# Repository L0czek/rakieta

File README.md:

Rakieta hardware
================

This repository contains the hardware and firmware for the rocket engine test project. It groups several PCBs and related firmware used for sensing, control distribution, ignition, and a crash-survivable blackbox recorder.

Subprojects

- `blackbox/`: Blackbox PCB (stores UART data to SD card)
- `blackbox-firmware/`: Firmware for the blackbox recorder
- `connector-main-computer/`: Connector board near controller that aggregates GPIO to a 10m DVI-I cable
- `connector-test-stand/`: Connector board at the test-stand end; decomposes signals, provides power, analog preprocessing, and actuators
- `esp32-mainboard/`: ESP32-C6 controller firmware as a git submodule on the `teststand` branch
- `frontend/`: Web UI for telemetry visualization and command/control; connects to MQTT over WebSocket
- `sensor-tmp107/`: TMP107 temperature sensor PCB (chainable via SMAART wire bus)
- `starter/`: Ignition starter board with I2C IO expander and safety comparator

Connection graph (Mermaid)

```mermaid
flowchart TB;
CONTROLLER["`CONTROLLER
esp32-mainboard`"] --- id(MAIN COMPUTER CONNECTOR)
CONTROLLER --- BLACKBOX
CONTROLLER ---|WiFi| MQTT[("`MQTT SERVER
eclipse-mosquitto`")]
id(MAIN COMPUTER CONNECTOR) --- id10(SAFETY BUTTON)
id(MAIN COMPUTER CONNECTOR) ---|10m DVI-I cable| id2(TEST STAND CONNECTOR)
id6(12V AGM battery) --- id2(TEST STAND CONNECTOR)
id2(TEST STAND CONNECTOR) --- id3(TEMP SENSOR 1)
id3(TEMP SENSOR 1) --- id4[[TEMP SENSOR 2...]]
id2(TEST STAND CONNECTOR) --- id5(STARTER)
id2(TEST STAND CONNECTOR) --- id7[[PRESSURE SENSORS 1 & 2]]
id2(TEST STAND CONNECTOR) --- id8(VALVE SERVO)
id2(TEST STAND CONNECTOR) --- id11(TENSOMETR)
id5(STARTER) --- id9(ENGINE IGNITION)
FRONTEND[[FRONTEND WEB UI]] --- MQTT
```

MQTT communication

- Broker: Mosquitto (`docker-compose.yml` service `mqtt`)
- Frontend: Docker Compose also launches the web dashboard on `http://localhost:3000`
- Controller (`esp32-mainboard`) publishes telemetry and receives command topics via MQTT
- Controller also publishes raw `defmt` log bytes on `log/defmt`
- The matching firmware ELF is shared as retained raw bytes on
  `shared/firmware/test_stand_controller/elf`
- Frontend connects to the same broker via WebSocket (`ws://<host>:8000`) and subscribes/publishes control topics
- MQTT TCP port: `1883` (standard MQTT)
- MQTT WebSocket port: `8000` (used by frontend)
- `mosquitto.conf` raises `max_packet_size` to `20000000` so the retained
  `shared/firmware/test_stand_controller/elf` payload can carry the matching firmware ELF

Publishing the retained ELF

Use the helper script after building the matching controller firmware ELF:

```bash
scripts/publish-test-stand-elf.sh \
  esp32-mainboard/target/riscv32imac-unknown-none-elf/debug/test_stand_controller
```

Set `MQTT_HOST`, `MQTT_PORT`, `MQTT_USERNAME`, `MQTT_PASSWORD`, or `MQTT_TOPIC` if you need
non-default broker settings.

Running with Docker Compose

```bash
git submodule update --init --recursive
docker compose up --build
```

The frontend is available at `http://localhost:3000`. The MQTT broker exposes TCP MQTT on
`1883` and WebSocket MQTT on `8000`.

Notes

- This repo is intended for hardware files (KiCad projects), gerbers and firmware sources related to the test-stand and engine instrumentation.
- See subdirectory READMEs for purpose and quick pointers to major files.

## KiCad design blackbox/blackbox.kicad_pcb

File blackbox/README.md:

Blackbox PCB
============

Purpose

The `blackbox` board is a crash-survivable data logger. It receives UART data from the controller and writes received data to an SD card so launch telemetry can be retrieved after a failure.

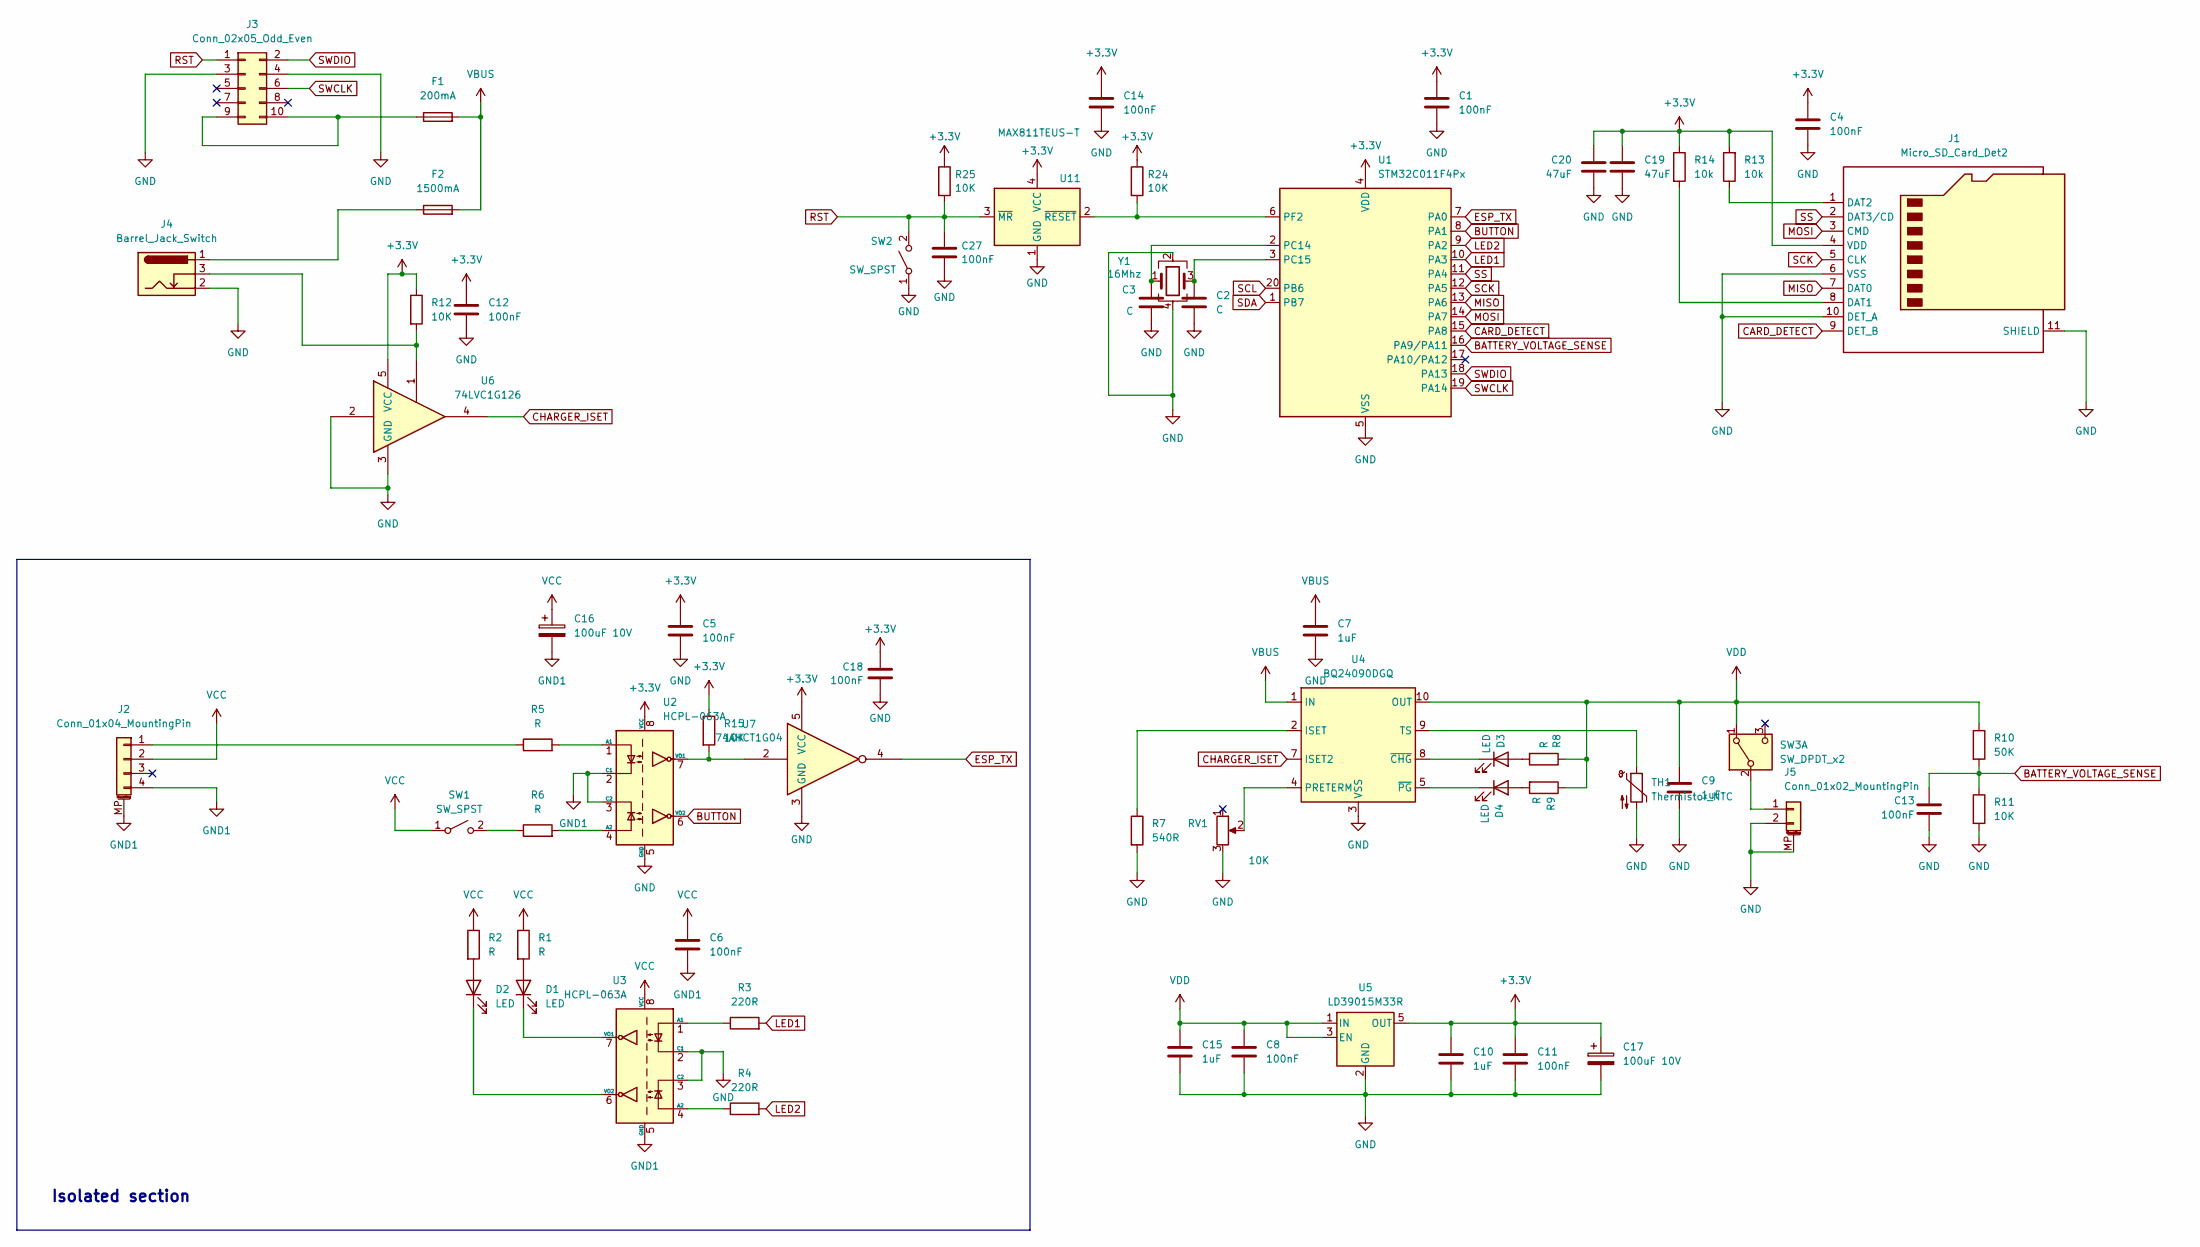
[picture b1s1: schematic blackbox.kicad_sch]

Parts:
C1, C4, C5, C6, C8, C11, C12, C13, C14, C18, C27: 100nF; C_0805_2012Metric
C2, C3: C; C_0805_2012Metric
C7, C9, C10, C15: 1uF; C_1206_3216Metric
C16, C17: 100uF 10V; CP_Elec_5x5.4
C19, C20: 47uF; C_1206_3216Metric
D1, D2: LED; LED_D5.0mm_Horizontal_O3.81mm_Z9.0mm
D3, D4: LED; LED_0805_2012Metric
F1: 200mA; Fuse_1206_3216Metric
F2: 1500mA; Fuse_1206_3216Metric
J1: Micro_SD_Card_Det2; microSD_HC_Hirose_DM3BT-DSF-PEJS
J2: Conn_01x04_MountingPin; JST_PH_S4B-PH-SM4-TB_1x04-1MP_P2.00mm_Horizontal
J3: Conn_02x05_Odd_Even; IDC-Header_2x05_P2.54mm_Vertical
J4: Barrel_Jack_Switch; BarrelJack_Horizontal
J5: Conn_01x02_MountingPin; JST_PH_S2B-PH-SM4-TB_1x02-1MP_P2.00mm_Horizontal
R1, R2, R5, R6, R8, R9: R; R_0805_2012Metric
R3, R4: 220R; R_0805_2012Metric
R7: 540R; R_0805_2012Metric
R10: 50K; R_0805_2012Metric
R11, R12, R15, R24, R25: 10K; R_0805_2012Metric
R13, R14: 10k; R_0805_2012Metric
RV1: 10K; Potentiometer_Bourns_3314J_Vertical
SW1: SW_SPST; SW_Tactile_SPST_Angled_PTS645Vx31-2LFS
SW2: SW_SPST; SW_SPST_B3S-1000
SW3: SW_DPDT_x2; SW_DPDT_CK_JS202011JCQN
TH1: Thermistor_NTC; R_0603_1608Metric
U1: STM32C011F4Px; TSSOP-20_4.4x6.5mm_P0.65mm
U2, U3: HCPL-063A; SOIC-8_3.9x4.9mm_P1.27mm
U4: BQ24090DGQ; IC_XTR111AIDGQR
U5: LD39015M33R; SOT-23-5
U6: 74LVC1G126; SOT-23-5
U7: 74AHCT1G04; SOT-23-5
U11: MAX811TEUS-T; SOT-143
Y1: 16Mhz; Crystal_SMD_3225-4Pin_3.2x2.5mm

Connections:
+3.3V: C1.1, C4.1, C5.1, C10.1, C11.1, C12.1, C14.1, C17.1, C18.1, C19.1, C20.1, J1.4 (VDD), R12.1, R13.2, R14.1, R15.1, R24.1, R25.1, U1.4 (VDD), U2.8 (VCC), U5.5 (OUT), U6.5 (VCC), U7.5 (VCC), U11.4 (VCC)
BATTERY_VOLTAGE_SENSE: C13.2, R10.2, R11.1, U1.16 (PA9/PA11)
BUTTON: U1.8 (PA1), U2.6 (VO2)
CARD_DETECT: J1.9 (DET_B), U1.15 (PA8)
CHARGER_ISET: U4.7 (ISET2), U6.4
ESP_TX: U1.7 (PA0), U7.4
GND: C1.2, C2.2, C3.2, C4.2, C5.2, C7.2, C8.2, C9.2, C10.2, C11.2, C12.2, C13.1, C14.2, C15.2, C17.2, C18.2, C19.2, C20.2, C27.2, J1.6 (VSS), J1.10 (DET_A), J1.11 (SHIELD), J3.3, J3.4, J4.2, J5.2, J5.MP (MountPin), R7.2, R11.2, RV1.3, SW2.1 (A), TH1.2, U1.5 (VSS), U2.5 (GND), U3.2 (C1), U3.3 (C2), U4.3 (VSS), U4.11 (VSS), U5.2 (GND), U6.2, U6.3 (GND), U7.3 (GND), U11.1 (GND), Y1.2, Y1.4
GND1: C6.2, C16.2, J2.4, J2.MP (MountPin), U2.2 (C1), U2.3 (C2), U3.5 (GND)
LED1: R3.2, U1.10 (PA3)
LED2: R4.2, U1.9 (PA2)
MISO: J1.7 (DAT0), U1.13 (PA6)
MOSI: J1.3 (CMD), U1.14 (PA7)
unnamed: D1.2 (A), R1.2
unnamed: D1.1 (K), U3.7 (VO1)
unnamed: D2.2 (A), R2.2
unnamed: D2.1 (K), U3.6 (VO2)
unnamed: D3.2 (A), R8.2
unnamed: D3.1 (K), U4.8 (~CHG)
unnamed: D4.2 (A), R9.2
unnamed: D4.1 (K), U4.5 (~PG)
unnamed: F2.1, J4.1
unnamed: J1.8 (DAT1), R14.2
unnamed: J1.1 (DAT2), R13.1
unnamed: J2.1, R5.1
unnamed: F1.1, J3.9, J3.10
unnamed: J4.3, R12.2, U6.1
unnamed: J5.1, SW3.2 (B)
unnamed: R6.1, SW1.2 (B)
unnamed: C3.1, U1.2 (PC14), Y1.1
unnamed: C2.1, U1.3 (PC15), Y1.3
unnamed: R24.2, U1.6 (PF2), U11.2 (~RESET)
unnamed: R5.2, U2.1 (A1)
unnamed: R6.2, U2.4 (A2)
unnamed: R15.2, U2.7 (VO1), U7.2
unnamed: R3.1, U3.1 (A1)
unnamed: R4.1, U3.4 (A2)
unnamed: R7.1, U4.2 (ISET)
unnamed: RV1.2, U4.4 (PRETERM)
unnamed: TH1.1, U4.9 (TS)
RST: C27.1, J3.1, R25.2, SW2.2 (B), U11.3 (~MR)
SCK: J1.5 (CLK), U1.12 (PA5)
SCL: U1.20 (PB6)
SDA: U1.1 (PB7)
SS: J1.2 (DAT3/CD), U1.11 (PA4)
SWCLK: J3.6, U1.19 (PA14)
SWDIO: J3.2, U1.18 (PA13)
VBUS: C7.1, F1.2, F2.2, U4.1 (IN)
VCC: C6.1, C16.1, J2.2, R1.1, R2.1, SW1.1 (A), U3.8 (VCC)
VDD: C8.1, C9.1, C15.1, R8.1, R9.1, R10.1, SW3.1 (A), U4.10 (OUT), U5.1 (IN), U5.3 (EN)

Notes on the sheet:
Isolated section

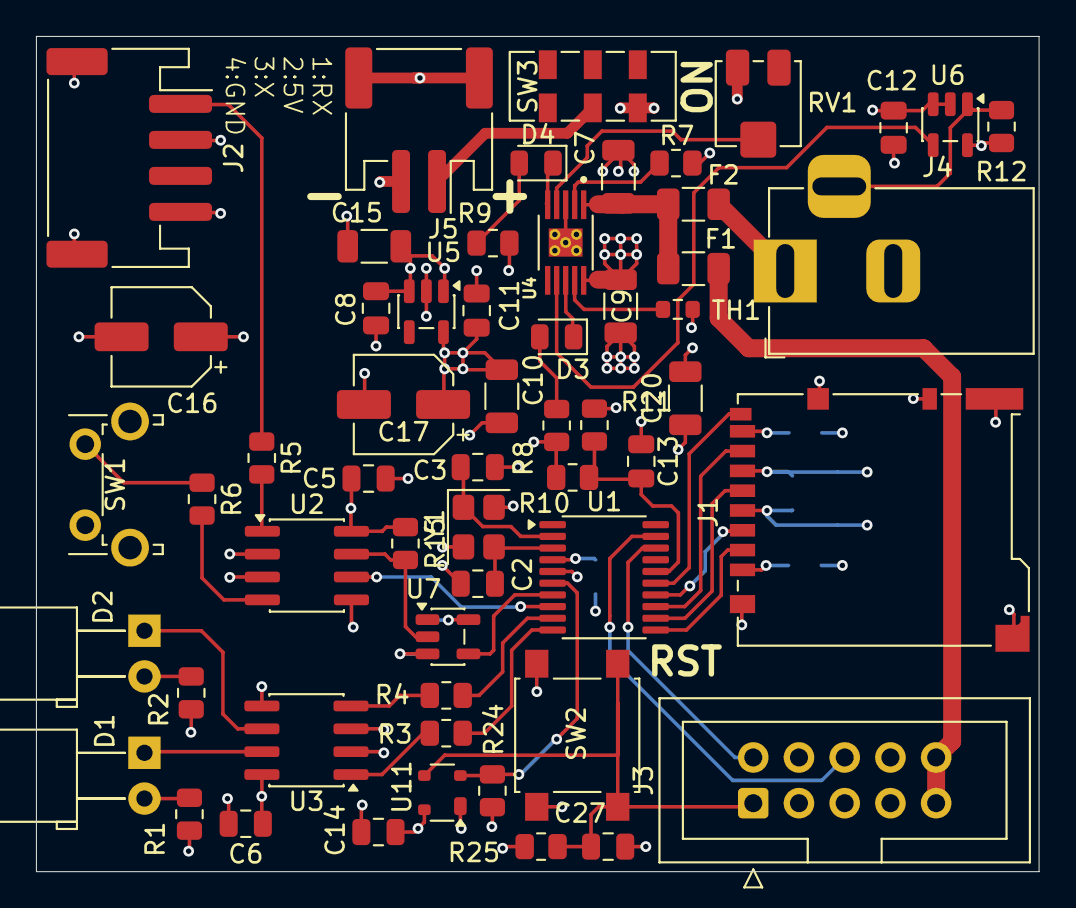
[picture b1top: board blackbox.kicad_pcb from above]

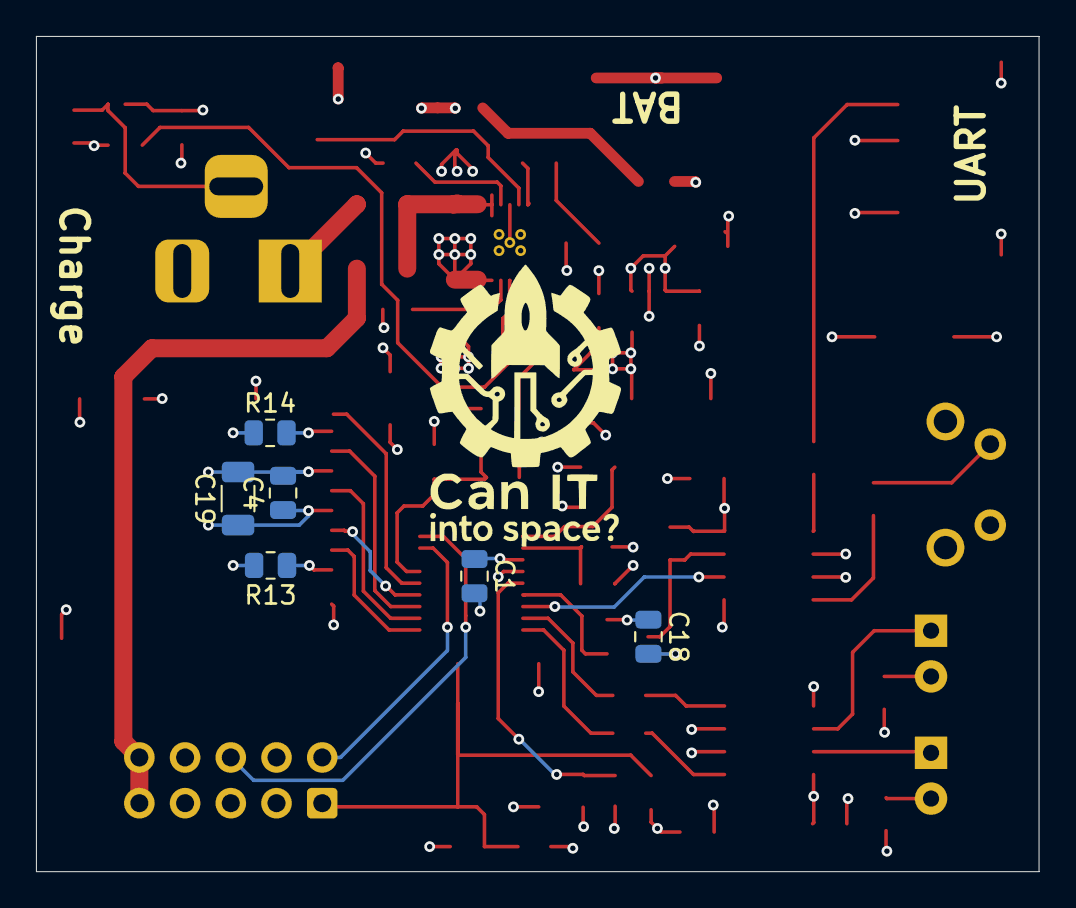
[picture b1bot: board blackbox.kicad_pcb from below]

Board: 4 copper layers, 55.7 x 46.4 mm, 63 parts (6 on the bottom side), 47 nets.

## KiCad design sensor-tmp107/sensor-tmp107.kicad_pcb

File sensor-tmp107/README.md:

TMP107 temperature sensor board
================================

Purpose

This board implements a temperature sensor using the TMP107 device. Multiple boards can be chained in series using the Ti SMAART wire bus (a UART half-duplex bus) to provide temperature sensing along the test-stand.

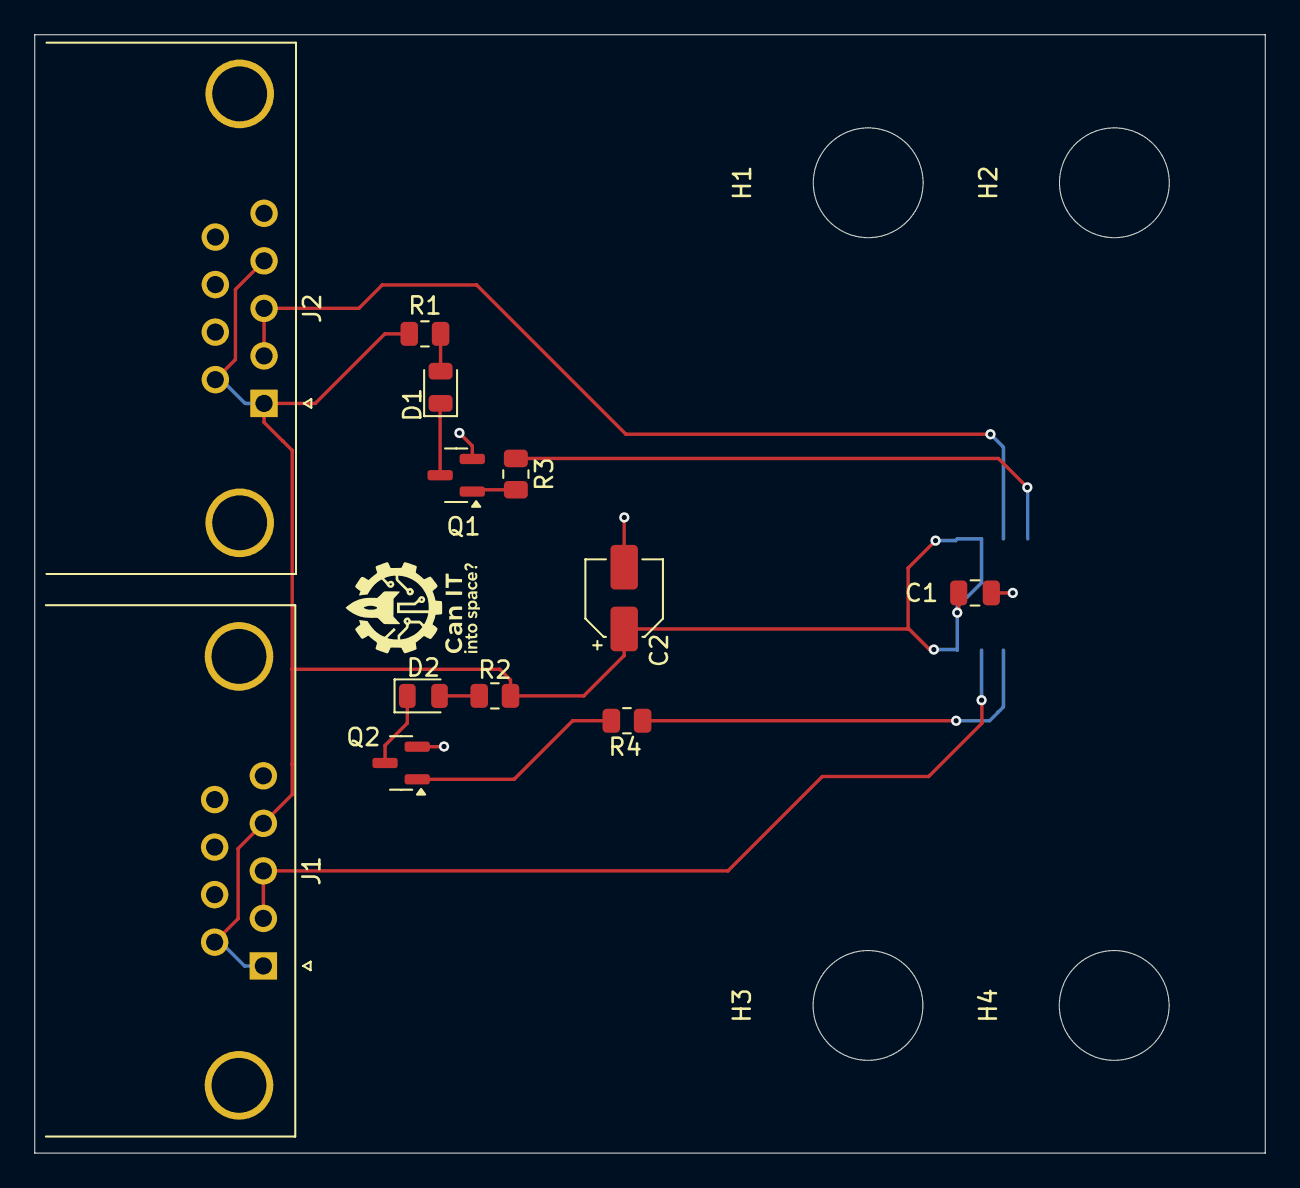
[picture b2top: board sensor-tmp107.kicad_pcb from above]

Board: 2 copper layers, 71.7 x 65.2 mm, 17 parts (1 on the bottom side), 12 nets.

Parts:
C1: 100nF; C_0805_2012Metric
C2: 10uF; CP_Elec_4x5.4
D1: LED żółtozielony; LED_0805_2012Metric
D2: LED czerwony; LED_0805_2012Metric
H1, H2, H3, H4: MountingHole_Pad_MP; MountingHole_6.4mm_M6
J1, J2: DE9_Socket_MountingHoles; DSUB-9_Socket_Horizontal_P2.77x2.84mm_EdgePinOffset9.90mm_H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
Q1, Q2: MMBT3904; SOT-23
R1, R2: 200; R_0805_2012Metric
R3, R4: 10k; R_0805_2012Metric
U1: TMP107BIDR; SOIC127P599X175-8N

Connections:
/5V: C1.1, C2.1, J1.1, J1.4, J1.6, J2.1, J2.4, J2.6, R1.1, R2.1, U1.1 (V+), U1.2 (R1), U1.8 (R2)
GND: C1.2, C2.2, J1.0 (PAD), J1.5, J1.7, J1.8, J1.9, J2.0 (PAD), J2.5, J2.7, J2.8, J2.9, Q1.2 (E), Q2.2 (E), U1.5 (GND)
unnamed: D1.2 (A), R1.2
unnamed: D1.1 (K), Q1.3 (C)
unnamed: D2.2 (A), R2.2
unnamed: D2.1 (K), Q2.3 (C)
unnamed: Q1.1 (B), R3.2
unnamed: Q2.1 (B), R4.1
unnamed: R3.1, U1.4 (ALERT1)
unnamed: R4.2, U1.6 (ALERT2)
unnamed: J2.2, J2.3, U1.3 (I/O1)
unnamed: J1.2, J1.3, U1.7 (I/O2)

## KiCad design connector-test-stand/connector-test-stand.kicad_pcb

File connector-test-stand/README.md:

Connector - test stand
======================

Purpose

This board is the test-stand end of the 10 m DVI-I cable. It decomposes the aggregated parallel bus into individual sensor and effector connectors, performs early analog preprocessing, provides power distribution, and drives actuators such as the valve servo.

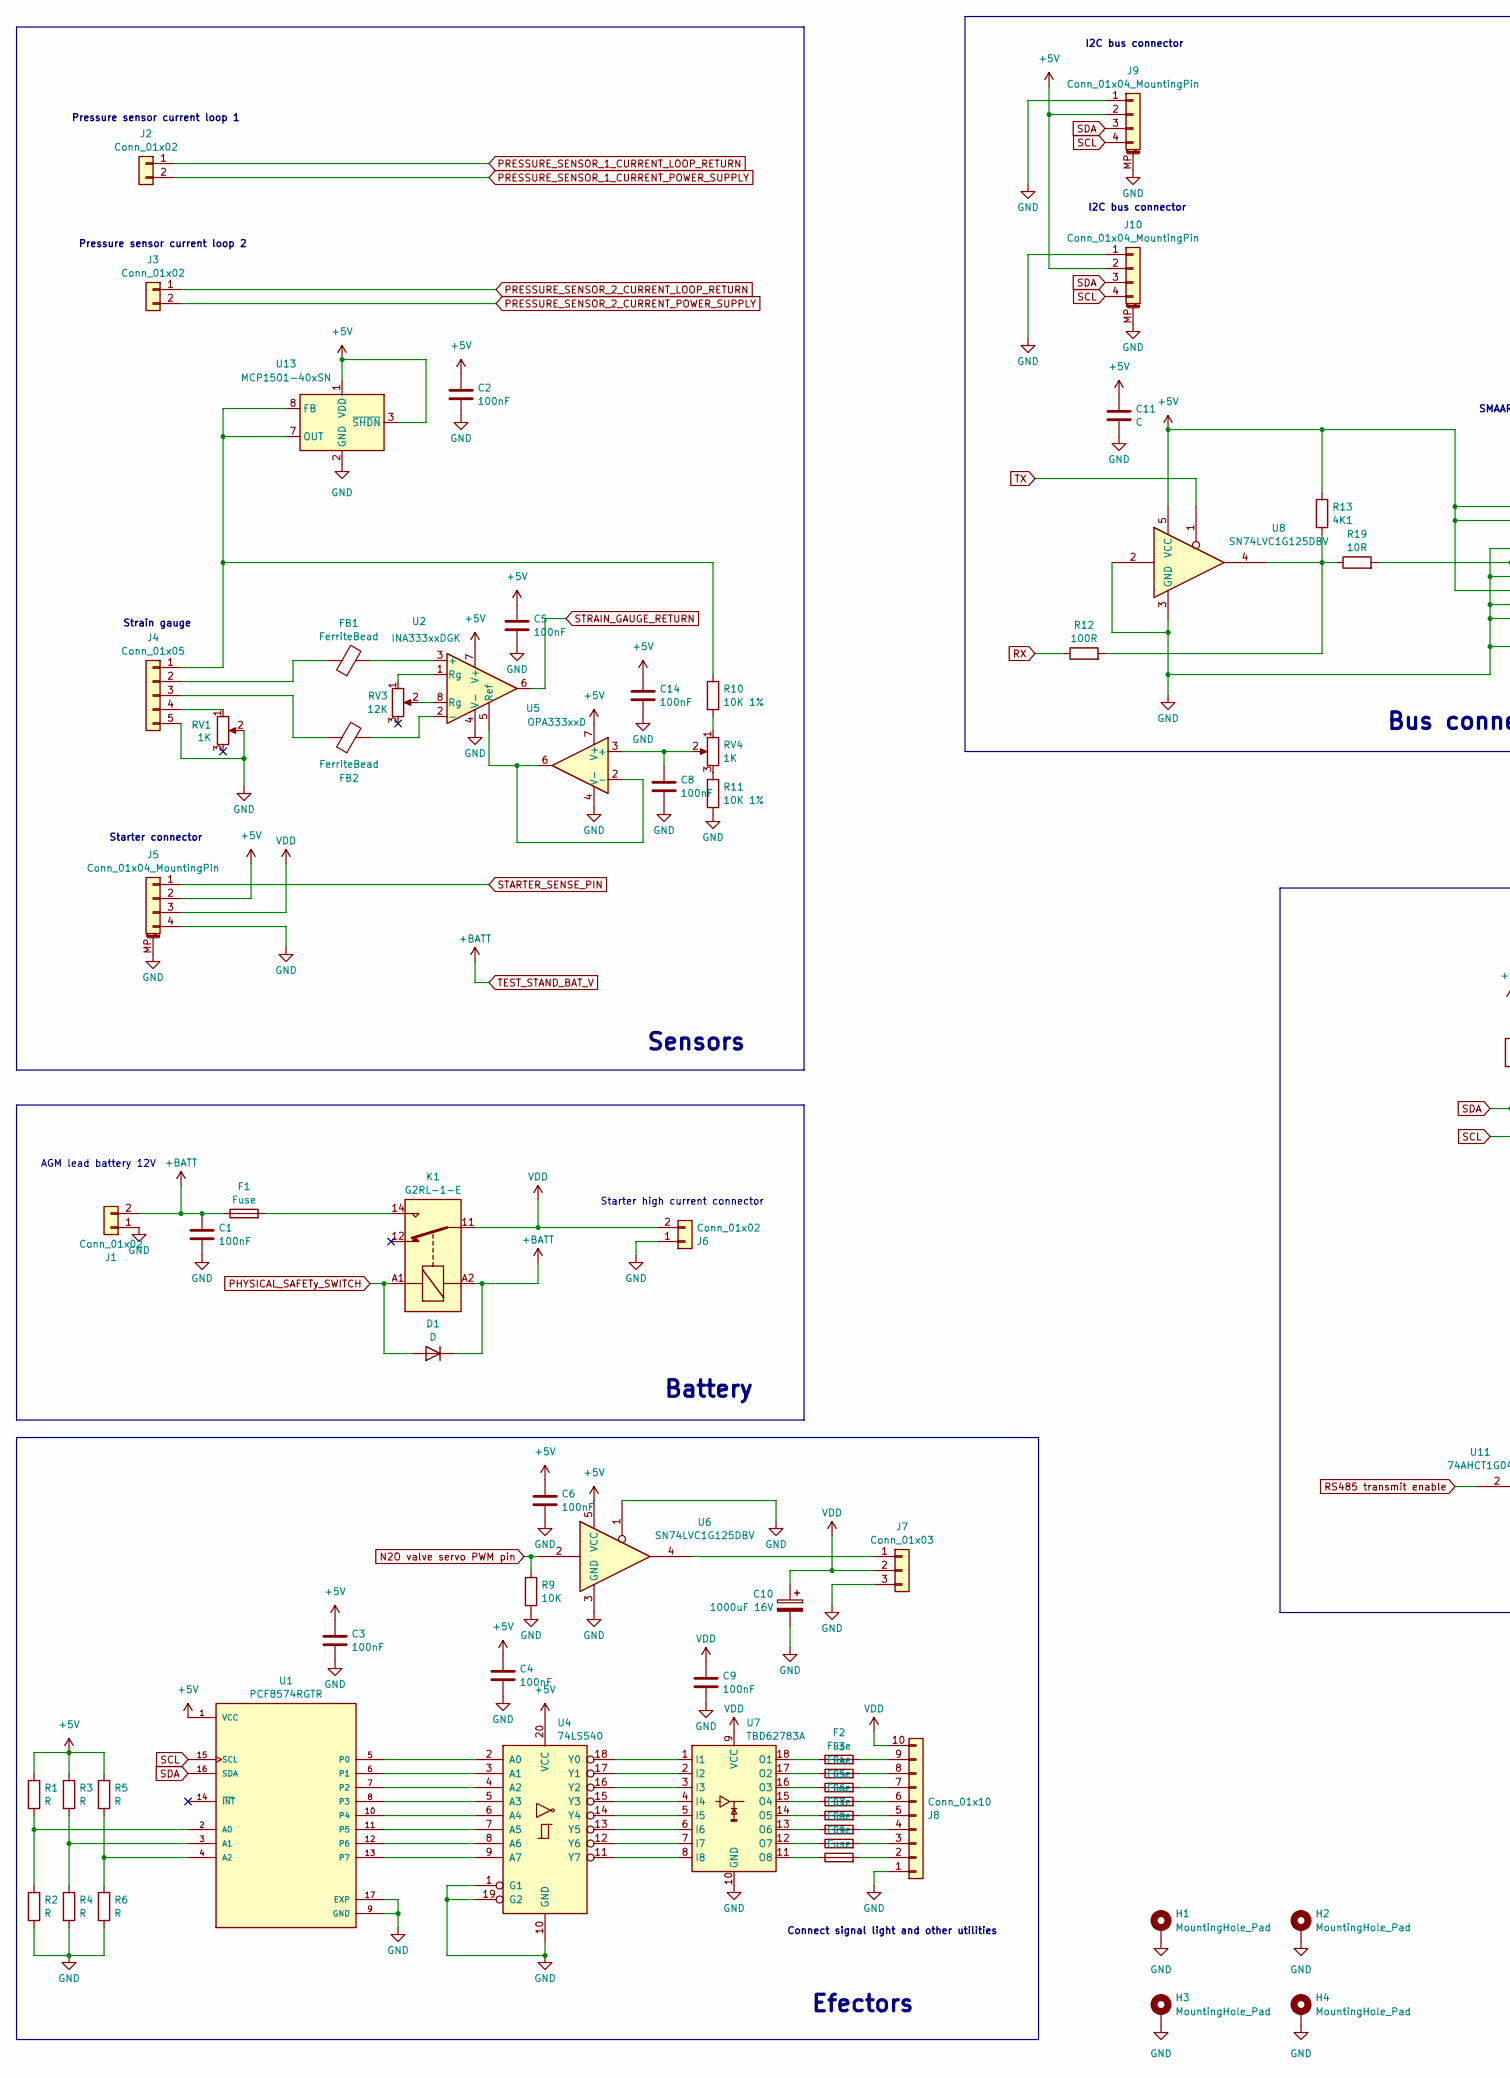
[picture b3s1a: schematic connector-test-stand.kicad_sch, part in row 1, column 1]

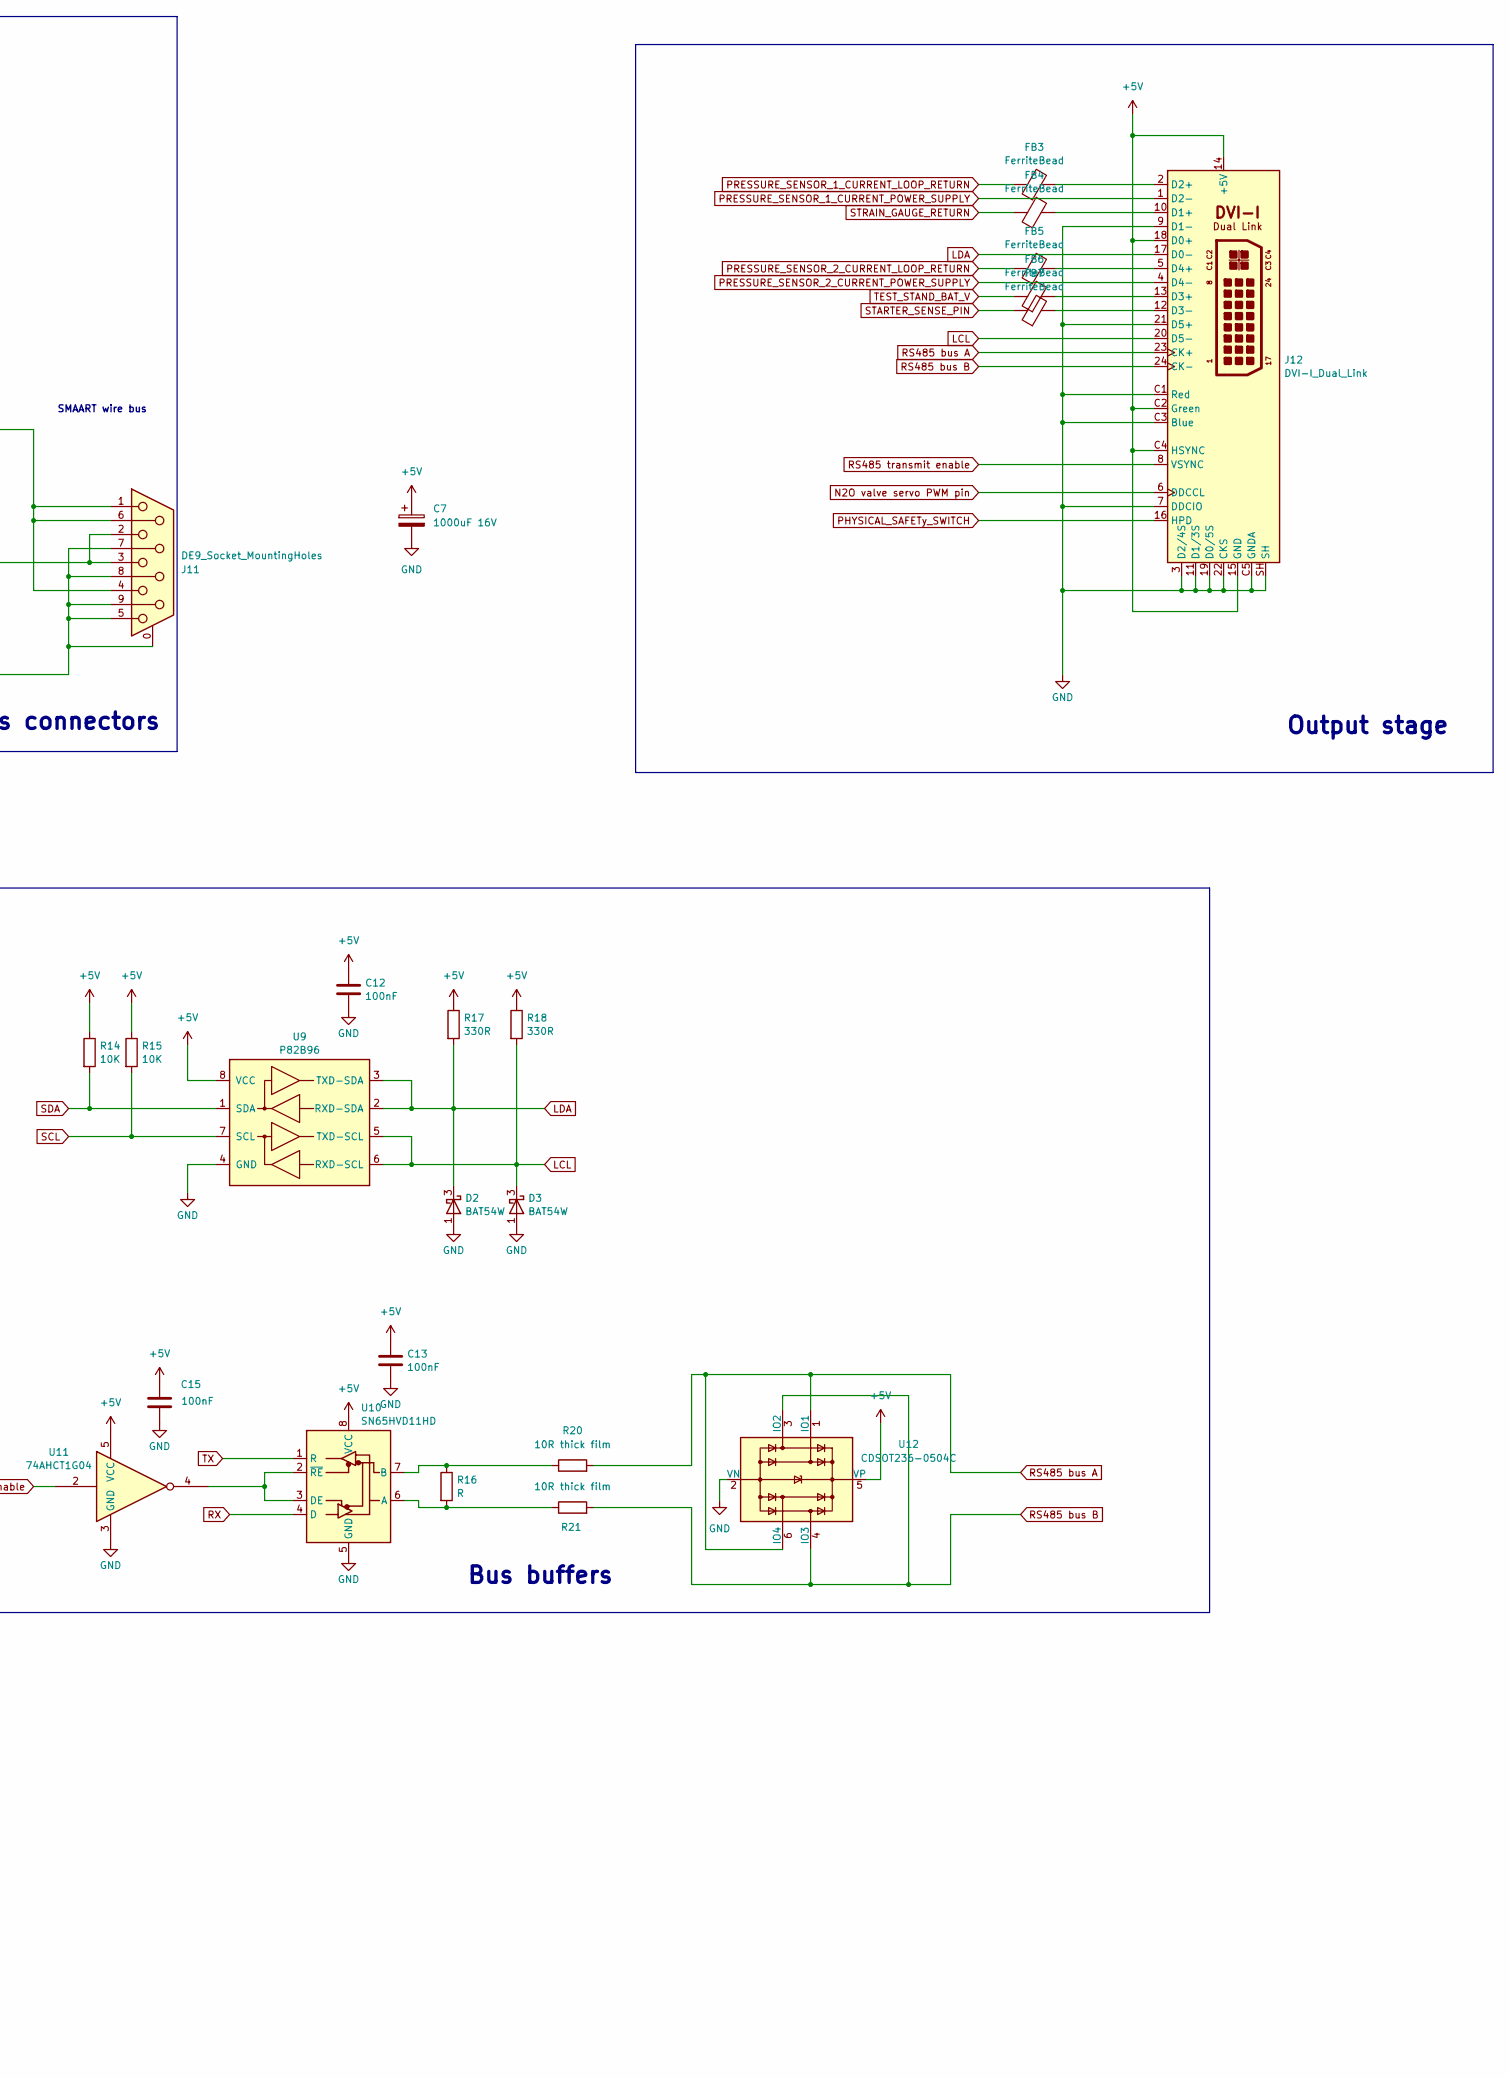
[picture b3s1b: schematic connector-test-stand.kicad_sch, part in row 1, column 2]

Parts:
C1, C2, C3, C4, C5, C6, C8, C9, C12, C13, C14, C15: 100nF; C_0805_2012Metric
C7, C10: 1000uF 16V; CP_Elec_10x10
C11: C; C_0805_2012Metric
D1: D; D_SMB
D2, D3: BAT54W; SOT-323_SC-70
F1: Fuse; Fuseholder_Cylinder-5x20mm_Bulgin_FX0456_Vertical_Closed
F2, F3, F4, F5, F6, F7, F8, F9: Fuse; Fuseholder_Clip-5x20mm_Schurter_CQM_Inline_P20.60x5.00mm_D1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
FB1, FB2, FB3, FB4, FB5, FB6, FB7: FerriteBead; L_0805_2012Metric
H1, H2, H3, H4: MountingHole_Pad; MountingHole_3.2mm_M3_Pad_Via
J1, J6: Conn_01x02; AMASS_XT30PW-M_1x02_P2.50mm_Horizontal
J2, J3: Conn_01x02; TerminalBlock_Altech_AK300-2_P5.00mm
J4: Conn_01x05; Altech_AK100_1x05_P5.00mm
J5, J9, J10: Conn_01x04_MountingPin; JST_PH_S4B-PH-SM4-TB_1x04-1MP_P2.00mm_Horizontal
J7: Conn_01x03; TerminalBlock_Altech_AK300-3_P5.00mm
J8: Conn_01x10; TerminalBlock_4Ucon_1x10_P3.50mm_Horizontal
J11: DE9_Socket_MountingHoles; DSUB-9_Socket_Horizontal_P2.77x2.84mm_EdgePinOffset9.90mm_H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
J12: DVI-I_Dual_Link; DVI-I_Molex_74320-1004_Horizontal
K1: G2RL-1-E; Relay_SPDT_Omron_G2RL-1-E
R1, R2, R3, R4, R5, R6, R16: R; R_0805_2012Metric
R9, R14, R15: 10K; R_0805_2012Metric
R10, R11: 10K 1%; R_0805_2012Metric
R12: 100R; R_0805_2012Metric
R13: 4K1; R_0805_2012Metric
R17, R18: 330R; R_0805_2012Metric
R19: 10R; R_0805_2012Metric
R20, R21: 10R thick film; R_0805_2012Metric
RV1, RV4: 1K; Potentiometer_Bourns_3266W_Vertical
RV3: 12K; Potentiometer_Bourns_3266W_Vertical
U1: PCF8574RGTR; QFN50P300X300X100-17N; PARTREV J; DigiKey_Part_Number 296-21238-2-ND
U2: INA333xxDGK; VSSOP-8_3x3mm_P0.65mm
U4: 74LS540; SO-20_12.8x7.5mm_P1.27mm
U5: OPA333xxD; SOIC-8_3.9x4.9mm_P1.27mm
U6, U8: SN74LVC1G125DBV; SOT-23-5
U7: TBD62783A; SOP-18_7x12.5mm_P1.27mm
U9: P82B96; SOIC-8_3.9x4.9mm_P1.27mm
U10: SN65HVD11HD; SOIC-8_3.9x4.9mm_P1.27mm
U11: 74AHCT1G04; SOT-23-5
U12: CDSOT236-0504C; SOT-23-6
U13: MCP1501-40xSN; SOIC-8_3.9x4.9mm_P1.27mm

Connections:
+5V: C2.1, C3.1, C4.1, C5.1, C6.1, C7.1, C11.1, C12.1, C13.1, C14.1, C15.1, J5.2, J9.2, J10.2, J11.1, J11.4, J11.6, J12.14 (+5V), J12.15 (GND), J12.18 (D0+), J12.C2 (Green), J12.C4 (HSYNC), R1.1, R3.1, R5.1, R13.1, R14.1, R15.1, R17.1, R18.1, U1.1 (VCC), U2.7 (V+), U4.20 (VCC), U5.7 (V+), U6.5 (VCC), U8.5 (VCC), U9.8 (VCC), U10.8 (VCC), U11.5 (VCC), U12.5 (VP), U13.1 (VDD), U13.3 (~SHDN)
GND: C1.2, C2.2, C3.2, C4.2, C5.2, C6.2, C7.2, C8.2, C9.2, C10.2, C11.2, C12.2, C13.2, C14.2, C15.2, D2.1 (A), D3.1 (A), H1.1, H2.1, H3.1, H4.1, J1.1, J4.5, J5.4, J5.MP (MountPin), J6.1, J7.3, J8.1, J9.1, J9.MP (MountPin), J10.1, J10.MP (MountPin), J11.0 (PAD), J11.5, J11.7, J11.8, J11.9, J12.3 (D2/4S), J12.7 (DDCIO), J12.9 (D1-), J12.11 (D1/3S), J12.19 (D0/5S), J12.21 (D5+), J12.22 (CKS), J12.C1 (Red), J12.C3 (Blue), J12.C5 (GNDA), J12.SH, R2.2, R4.2, R6.2, R9.2, R11.2, RV1.2, U1.9 (GND), U1.17 (EXP), U2.4 (V-), U4.1 (G1), U4.10 (GND), U4.19 (G2), U5.4 (V-), U6.1, U6.3 (GND), U7.10 (GND), U8.2, U8.3 (GND), U9.4 (GND), U10.5 (GND), U11.3 (GND), U12.2 (VN), U13.2 (GND), U13.4 (GND), U13.5 (GND), U13.6 (GND)
LCL: D3.3 (K), J12.20 (D5-), R18.2, U9.5 (TXD-SCL), U9.6 (RXD-SCL)
LDA: D2.3 (K), J12.17 (D0-), R17.2, U9.2 (RXD-SDA), U9.3 (TXD-SDA)
N2O valve servo PWM pin: J12.6 (DDCCL), R9.1, U6.2
unnamed: F1.2, K1.14
unnamed: J4.1, R10.1, U13.7 (OUT), U13.8 (FB)
unnamed: FB1.1, J4.2
unnamed: FB2.1, J4.3
unnamed: J4.4, RV1.1
unnamed: J7.1, U6.4
unnamed: F9.2, J8.2
unnamed: F8.2, J8.3
unnamed: F7.2, J8.4
unnamed: F6.2, J8.5
unnamed: F5.2, J8.6
unnamed: F4.2, J8.7
unnamed: F3.2, J8.8
unnamed: F2.2, J8.9
unnamed: J11.2, J11.3, R19.2
unnamed: FB4.2, J12.10 (D1+)
unnamed: FB3.2, J12.2 (D2+)
unnamed: FB6.2, J12.13 (D3+)
unnamed: FB7.2, J12.12 (D3-)
unnamed: FB5.2, J12.5 (D4+)
unnamed: R10.2, RV4.1
unnamed: R11.1, RV4.3
unnamed: R12.2, R13.2, R19.1, U8.4
unnamed: RV3.1, U2.1 (Rg)
unnamed: RV3.2, U2.8 (Rg)
unnamed: R1.2, R2.1, U1.2 (A0)
unnamed: R3.2, R4.1, U1.3 (A1)
unnamed: R5.2, R6.1, U1.4 (A2)
unnamed: U1.5 (P0), U4.2 (A0)
unnamed: U1.6 (P1), U4.3 (A1)
unnamed: U1.7 (P2), U4.4 (A2)
unnamed: U1.8 (P3), U4.5 (A3)
unnamed: U1.10 (P4), U4.6 (A4)
unnamed: U1.11 (P5), U4.7 (A5)
unnamed: U1.12 (P6), U4.8 (A6)
unnamed: U1.13 (P7), U4.9 (A7)
unnamed: FB1.2, U2.3 (+)
unnamed: FB2.2, U2.2 (-)
unnamed: U2.5 (Ref), U5.2 (-), U5.6
unnamed: U4.18 (Y0), U7.1 (I1)
unnamed: U4.17 (Y1), U7.2 (I2)
unnamed: U4.16 (Y2), U7.3 (I3)
unnamed: U4.15 (Y3), U7.4 (I4)
unnamed: U4.14 (Y4), U7.5 (I5)
unnamed: U4.13 (Y5), U7.6 (I6)
unnamed: U4.12 (Y6), U7.7 (I7)
unnamed: U4.11 (Y7), U7.8 (I8)
unnamed: C8.1, RV4.2, U5.3 (+)
unnamed: F2.1, U7.18 (O1)
unnamed: F3.1, U7.17 (O2)
unnamed: F4.1, U7.16 (O3)
unnamed: F5.1, U7.15 (O4)
unnamed: F6.1, U7.14 (O5)
unnamed: F7.1, U7.13 (O6)
unnamed: F8.1, U7.12 (O7)
unnamed: F9.1, U7.11 (O8)
unnamed: R16.2, R21.1, U10.6 (A)
unnamed: R16.1, R20.1, U10.7 (B)
unnamed: U10.2 (~RE), U10.3 (DE), U11.4
PHYSICAL_SAFETy_SWITCH: D1.2 (A), J12.16 (HPD), K1.A1
PRESSURE_SENSOR_1_CURRENT_LOOP_RETURN: FB3.1, J2.1
PRESSURE_SENSOR_1_CURRENT_POWER_SUPPLY: J2.2, J12.1 (D2-)
PRESSURE_SENSOR_2_CURRENT_LOOP_RETURN: FB5.1, J3.1
PRESSURE_SENSOR_2_CURRENT_POWER_SUPPLY: J3.2, J12.4 (D4-)
RS485 bus A: J12.23 (CK+), R20.2, U12.1 (IO1), U12.6 (IO4)
RS485 bus B: J12.24 (CK-), R21.2, U12.3 (IO2), U12.4 (IO3)
RS485 transmit enable: J12.8 (VSYNC), U11.2
RX: R12.1, U10.4 (D)
SCL: J9.4, J10.4, R15.2, U1.15 (SCL), U9.7 (SCL)
SDA: J9.3, J10.3, R14.2, U1.16 (SDA), U9.1 (SDA)
STARTER_SENSE_PIN: FB7.1, J5.1
STRAIN_GAUGE_RETURN: FB4.1, U2.6
TEST_STAND_BAT_V: C1.1, D1.1 (K), F1.1, FB6.1, J1.2, K1.A2
TX: U8.1, U10.1 (R)
VDD: C9.1, C10.1, J5.3, J6.2, J7.2, J8.10, K1.11, U7.9 (VCC)

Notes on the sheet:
Efectors
Sensors
Bus connectors
Starter connector
Output stage
Pressure sensor current loop 2
Connect signal light and other utilities
SMAART wire bus
Starter high current connector
Battery
I2C bus connector
AGM lead battery 12V
Bus buffers
Strain gauge
Pressure sensor current loop 1

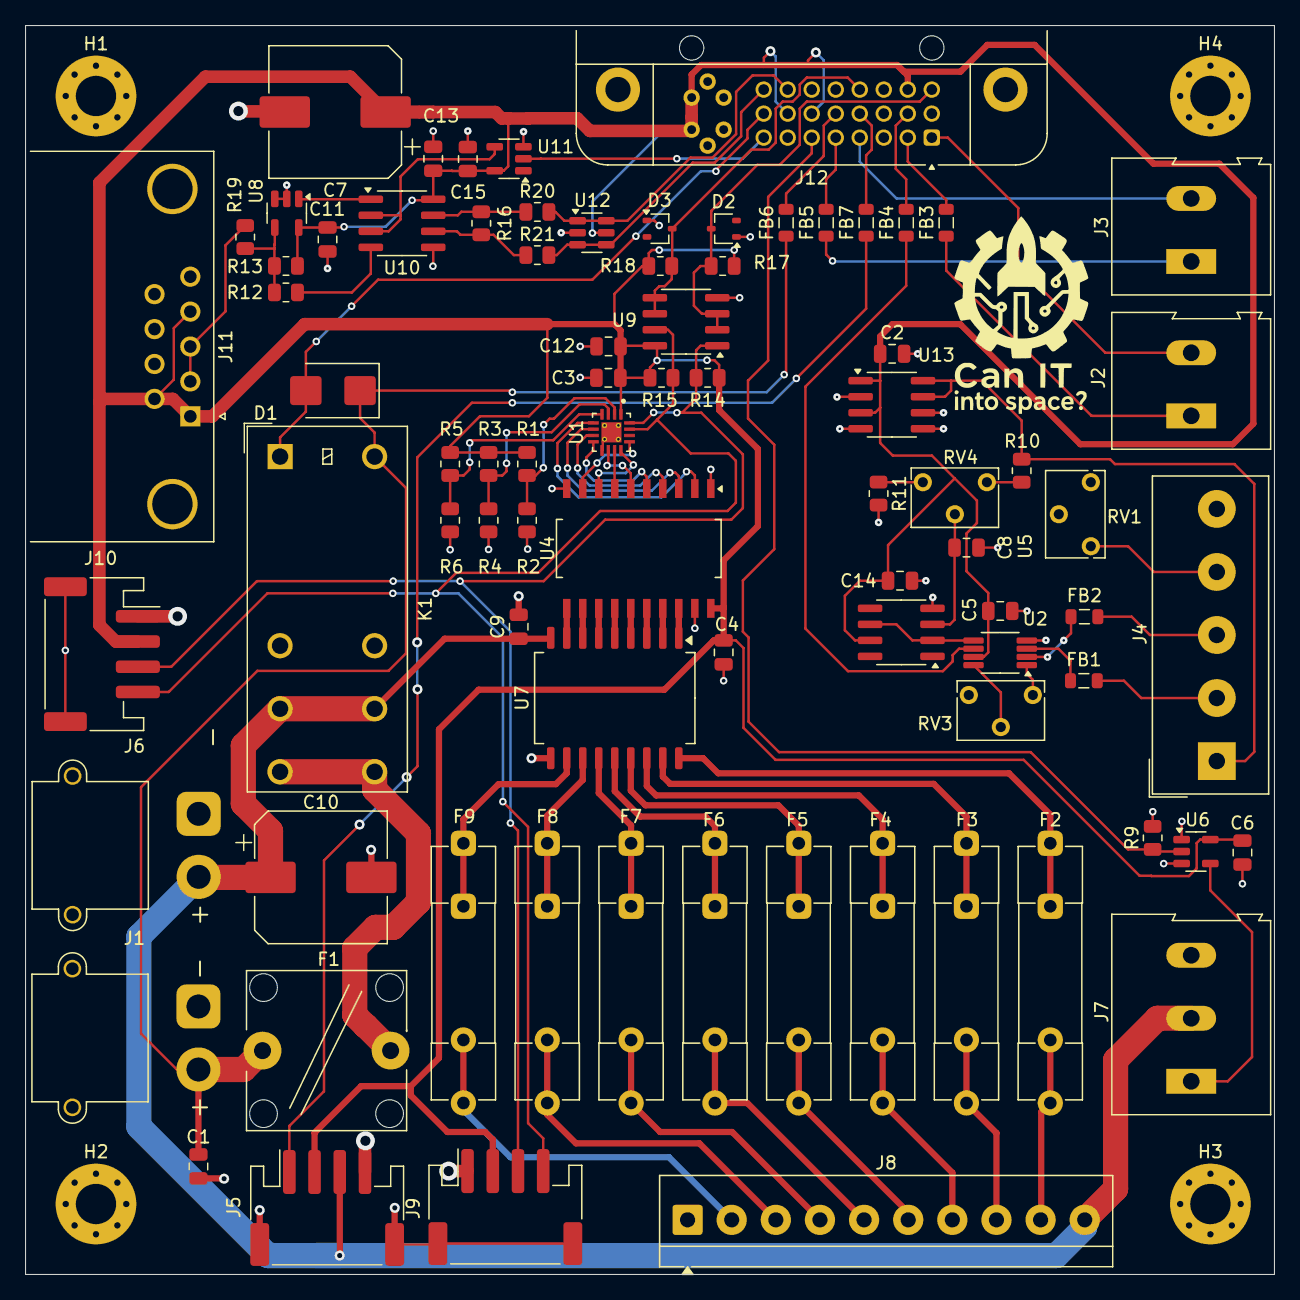
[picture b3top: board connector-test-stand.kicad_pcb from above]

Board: 2 copper layers, 99.1 x 99.1 mm, 85 parts (0 on the bottom side), 80 nets.
